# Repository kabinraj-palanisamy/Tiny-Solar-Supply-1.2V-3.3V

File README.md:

# Tiny Solar Supply — 1.2V to 3.3V Boost Converter
A compact solar-powered boost converter PCB built in KiCad,
based on the Elektor design by Clemens Valens (Circuit Special 2023).

## Overview
Converts a 1.2V Ni-MH AA battery (charged via solar panel) into a
regulated 3.3V output suitable for microcontroller applications.
Includes automatic day/night switching via 2N7002 MOSFET.

## Specifications
- Input voltage: 1V – 12V
- Output voltage: 3.3V regulated
- Max output current: 100mA (AP3015A)
- Switching IC: AP3015 micropower step-up DC/DC converter

## Tools
KiCad 10.0.1

## Credit
Original circuit design: Clemens Valens, Elektor Circuit Special 2023

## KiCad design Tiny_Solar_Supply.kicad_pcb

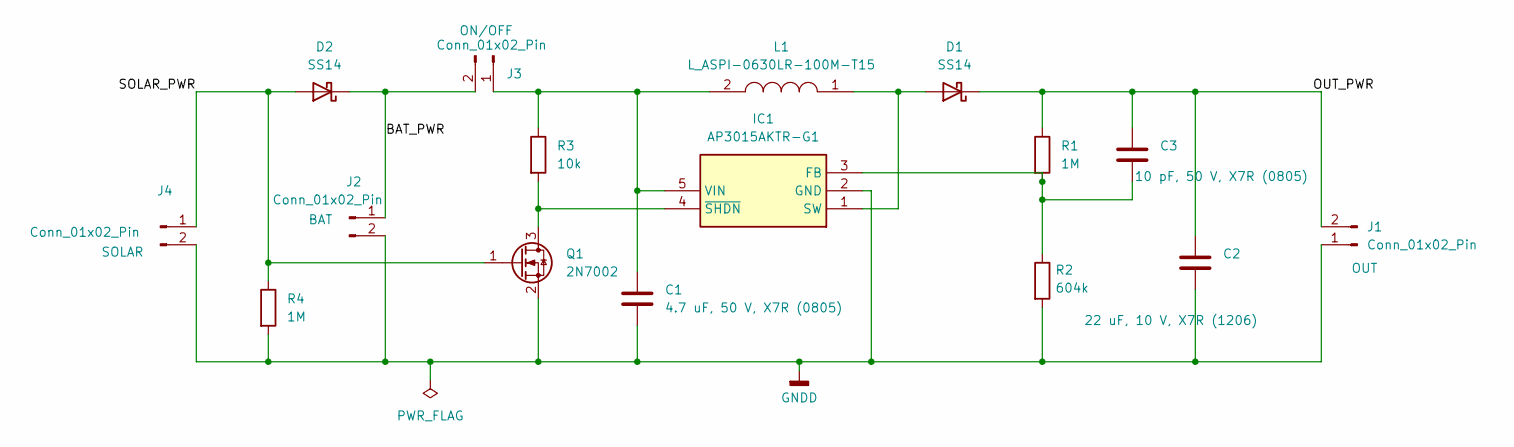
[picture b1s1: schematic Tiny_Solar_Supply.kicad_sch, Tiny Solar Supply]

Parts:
C1: 4.7 uF, 50 V, X7R (0805); C_0805_2012Metric
C2: 22 uF, 10 V, X7R (1206); C_0805_2012Metric
C3: 10 pF, 50 V, X7R (0805); C_0805_2012Metric
D1, D2: SS14; D_SMA
IC1: AP3015AKTR-G1; MCU_AP3015AKTR-G1; Manufacturer_Part_Number AP3015AKTR-G1; Mouser Part Number 621-AP3015AKTR-G1
J1, J2, J3, J4: Conn_01x02_Pin; PinSocket_1x02_P2.54mm_Vertical
L1: L_ASPI-0630LR-100M-T15; L_ASPI-0630LR
Q1: 2N7002; SOT-23
R1, R4: 1M; R_0805_2012Metric
R2: 604k; R_0805_2012Metric
R3: 10k; R_0805_2012Metric

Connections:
/BAT_PWR: D2.1 (K), J2.1, J3.2
/OUT_PWR: C2.1, C3.1, D1.1 (K), J1.2, R1.1
/SOLAR_PWR: D2.2 (A), J4.1, Q1.1 (G), R4.1
GNDD: C1.2, C2.2, IC1.2 (GND), J1.1, J2.2, J4.2, Q1.2 (S), R2.2, R4.2
unnamed: D1.2 (A), IC1.1 (SW), L1.1
unnamed: C3.2, IC1.3 (FB), R1.2, R2.1
unnamed: C1.1, IC1.5 (VIN), J3.1, L1.2, R3.1
unnamed: IC1.4 (~SHDN), Q1.3 (D), R3.2

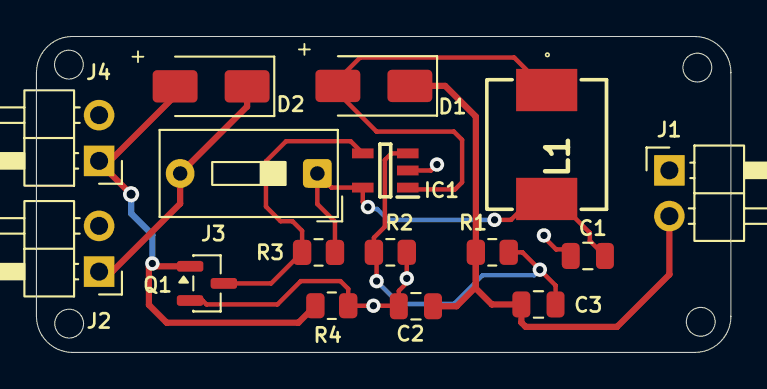
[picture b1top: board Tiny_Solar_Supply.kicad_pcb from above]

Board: 2 copper layers, 38.6 x 17.6 mm, 16 parts (0 on the bottom side), 8 nets.

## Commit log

2026-06-28 Add files via upload
    Schematic
2026-06-28 Schematic
2026-06-28 Gerber Files
